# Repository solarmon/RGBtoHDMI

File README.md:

# RGBtoHDMI
RGBtoHDMI Projects

Various PCB projects based on c0pperdragon's Amiga adapter for hogetlet67's RGBtoHDMI solution to provide a HDMI output from the Denise chip digital signals on Amiga computers.

https://github.com/c0pperdragon/Amiga-Digital-Video

https://github.com/hoglet67/RGBtoHDMI

## Issues and Questions

Any issues or questions, please raise a ticket in the **Issues** section:

https://github.com/solarmon/RGBtoHDMI/issues

## Requirements

* Any Raspberry Pi Zero variant, but please note the following:
 - Raspberry Pi Zero 1.3 (original, no wireless, without a header, typically only one per purchase allowed)
 - Raspberry Pi Zero W (with **Wireless**, no header)
 - Raspberry Pi Zero WH (with **Wireless**, with **Header**)
* HDMI adapter/cable: 
 -The Raspberry Pi Zero comes with a **mini-HDMI** interface.
 - This needs needs to be mounted somewhere on, or passed through, the case.

## Audio not supported

The current RGBtoHDMI solutions do not support audio.

You will need to get audio to the HDMI display using some other method.

## OCS Display Modes Only

Only **OCS** display modes are supported, even when an ECS Denise is used.

**ECS** or **AGA** display modes are **not supported**.

## RGBtoHDMI Firmware for Raspberry Pi Zero

The official RGBtoHDMI firmware for the Raspberry Pi Zero can be downloaded from:

https://github.com/hoglet67/RGBtoHDMI/releases

Extract the zip file to the root of the micro-SD card.

Beta releases from IanSB can be downloaded from: 

https://github.com/IanSB/RGBtoHDMI/releases

These releases are sometimes required for certain features to work.

---
## CPLD Based Designs ##

These CPLD based boards are based on RGBtoHDMI CPLD design by LinuxJedi:

https://github.com/LinuxJedi/AmigaRGBtoHDMI

These don't require a Denise OCS/ECS jumper and have three menu button support.

I have added FF OSD integration support to the board.

A Quick Start Guide for these CPLD boards cane be found at:

https://github.com/solarmon/RGBtoHDMI/wiki/RGBtoHDMI-CPLD-Quick-Start-Guide

### RGBtoHDMI Amiga Denise DIP CPLD Rev 1.1 ###

More details and design files:

Rev 1.1: https://github.com/solarmon/RGBtoHDMI/tree/main/CPLD/RGBtoHDMI%20Amiga%20Denise%20DIP%20CPLD%20Rev%201.1

Rev 1.1 adds an optional additional right-angle push button for BT1.

Older revisions:

Rev 1.0: https://github.com/solarmon/RGBtoHDMI/tree/main/CPLD/RGBtoHDMI%20Amiga%20Denise%20DIP%20CPLD

## CPLD and FFC Based Designs ##

These CPLD based boards are based on the excellent RGBtoHDMI CPLD design by LinuxJedi:

https://github.com/LinuxJedi/AmigaRGBtoHDMI

These don't require a Denise OCS/ECS jumper and have three menu button support.

I have added FF OSD integration support to the board.

I have used an FFC connector design to allow for different breakout hats for different Denise packages (PLCC and DIP).

### RGBtoHDMI Amiga Denise CPLD FFC Rev 1.1 ###

More details and design files:

Rev 1.1: https://github.com/solarmon/RGBtoHDMI/tree/main/CPLD/RGBtoHDMI%20Amiga%20Denise%20CPLD%20FFC%20Rev%201.1

Rev 1.1 adds an optional additional right-angle push button for BT1.

Older revisions:

Rev 1.0: https://github.com/solarmon/RGBtoHDMI/tree/main/CPLD/RGBtoHDMI%20Amiga%20Denise%20CPLD%20FFC

### RGBtoHDMI Amiga Denise PLCC SMT Breakout FFC ###

More details and design files: https://github.com/solarmon/RGBtoHDMI/tree/main/CPLD/RGBtoHDMI%20Amiga%20Denise%20PLCC%20SMT%20Breakout%20FFC

### RGBtoHDMI Amiga Denise DIP Breakout FFC ###

More details and design files: https://github.com/solarmon/RGBtoHDMI/tree/main/CPLD/RGBtoHDMI%20Amiga%20Denise%20DIP%20Breakout%20FFC

### FF OSD Adapter - Rev 2 ##

More details and design files: https://github.com/solarmon/FlashFloppy/tree/main/FF%20OSD%20Adapter%20-%20Rev%202

The CPLD based RGBtoHDMI boards support FlashFloppy OSD integration and this is made easier with the FF OSD Adapter Rev 2 adapter.

---

## Amiga Denise DIP Adapter v2++

KiCAD design files:

https://github.com/solarmon/RGBtoHDMI/tree/main/RGBtoHDMI%20Amiga%20Denise%20-%20v2%2B%2B%20by%20solarmon

Based on on c0pperdragon's v2 adapter

https://github.com/c0pperdragon/Amiga-Digital-Video

https://github.com/hoglet67/RGBtoHDMI/tree/master/kicad_AmigaAdapter/V2

Tweaks and additions:

* Tweak to mask clearances
* Top and bottom ground plane
* Removes +3.3V regulator and uses the Raspberry Pi Zero +3.3V regulator
* Optional delay on PiCLK signal
* Support for FlashFloppy OSD

**Note**: The optional delay circuit (**U4**) for the **PiCLK** signal does not seem to do anything, so it is redundant and not required (but **JP2** still needs to be set to '**Normal PiCLK**'). It will be removed from future versions.

FlashFloppy OSD support is best used with the FlashFloppy OSD Blue Pill adapter at:

https://github.com/solarmon/FlashFloppy/tree/main/FF%20OSD%20Adapter

## Amiga Denise DIP Adapter v2++ Rev 2

KiCAD design files:

https://github.com/solarmon/RGBtoHDMI/tree/main/RGBtoHDMI%20Amiga%20Denise%20-%20v2%2B%2B%20by%20solarmon%20-%20Rev%202

This rev 2 design removes the redundant delay circuit using logic inverters, but adds the option to add a 47pF cap to the PiCLK line.

## Amiga Denise DIP Adapter - With Pi Relocation - Rev 1

**Note:** This is the **Rev 1** design - see further down for the **Rev 2** design.

**WARNING:** Uses an **SMT** socket header for the Raspberry Pi Zero

KiCAD design files:

https://github.com/solarmon/RGBtoHDMI/tree/main/RGBtoHDMI%20Amiga%20Denise%20-%20solarmon

A complete PCB redesign of the Amiga RGBtoHDMI v2 adapter by c0pperdragon.

Features:

* Raspberry Pi relocated to sit above the Odd CIA chip
* Use the Raspberry Pi Zero +3.3V regulator
* Optional delay on PiCLK signal
* Support for FlashFloppy OSD
* Uses an **SMT** socket header for the Raspberry Pi Zero

FlashFloppy OSD support is best used with the FlashFloppy OSD Blue Pill adapter at:

https://github.com/solarmon/FlashFloppy/tree/main/FF%20OSD%20Adapter

**Note**: The optional delay circuit (**U4**) for the **PiCLK** signal does not seem to do anything, so it is redundant and not required (but **JP2** still needs to be set to '**Normal PiCLK**'). It will be removed from future versions.

**Note**: **IMPORTANT** On this board design the Raspberry Pi Zero faces **up**. This is different from the original RGBtoHDMI v2 adapter where it faces **down**. This means the header is on the other side, so any existing Raspberry Pi Zero will need to be modified accordingly. **This will be changed in the next version to face down, so that existing Raspberry Pi Zeros can be used.**

**Note**: This board design still uses the smaller **TSSOP** package from the original RGBtoHDMI adapter. The next version will use the larger **SOIC** package.

## Amiga Denise DIP Adapter - With Pi Relocation - Rev 2 (TSSOP)

**WARNING:** Uses an **SMT** socket header for the Raspberry Pi Zero

KiCAD design files:

https://github.com/solarmon/RGBtoHDMI/tree/main/RGBtoHDMI%20Amiga%20Denise%20-%20solarmon%20-%20Rev%202%20-%20TSSOP

**Note:** This Rev 2 design has the Pi Zero facing **DOWN** (instead of facing **UP** in rev 1)

This rev 2 design removes the redundant delay circuit using logic inverters, but adds the option to add a 47pF cap to the PiCLK line.

This design still uses the smaller **TSSOP** chip package.

## Amiga Denise DIP Adapter - With Pi Relocation - Rev 2 (SOIC)

**WARNING:** Uses an **SMT** socket header for the Raspberry Pi Zero

KiCAD design files:

https://github.com/solarmon/RGBtoHDMI/tree/main/RGBtoHDMI%20Amiga%20Denise%20-%20solarmon%20-%20Rev%202%20-%20SOIC

**Note:** This Rev 2 design has the Pi Zero facing **DOWN** (instead of facing **UP** in rev 1)

**Note:** This version uses the larger SOIC chip package

This rev 2 design removes the redundant delay circuit using logic inverters, but adds the option to add a 47pF cap to the PiCLK line.

This design still uses the larger **SOIC** chip package, making it easier to hand solder.

## Amiga Denise PLCC Adapter

KiCAD design files:

https://github.com/solarmon/RGBtoHDMI/tree/main/RGBtoHDMI%20Amiga%20Denise%20ECS%20PLCC

Based on c0pperdragon's RGBtoHDMI Small adapter.

https://github.com/hoglet67/RGBtoHDMI/tree/master/kicad_AmigaAdapter/Small

This is a PLCC hat version of the RGBtoHDMI Small adapter that sits directly on top of the Denise PLCC chip.

This is for the Amiga A600 Denise ECS chip. However, the RGBtoHDMI solution only supports **OCS** modes, not **ECS** modes:

https://github.com/c0pperdragon/Amiga-Digital-Video#compatibility

**Note**: It uses the larger **SOIC** chip package, rather than the smaller **TSSOP** chip package.

Features:

* No soldering required - sits directly on top of the Denise PLCC chip
* Integrated RGBtoHDMI solution on same board.

**Note**: The +**5V** and **GND** traces going to the Denise PLCC chip is very thin. Header **JP1** is provided for +**5V** and **GND**. It is recommedned that power is provided to the board using this.

**Note**: The PLCC socket on this board needs some midifications to allow it to sit properly. See LemaruX's guide on the 68K PLCC socket rework that also applies to the Denise PLCC socket: 

https://github.com/LemaruX/Amiga-A600-68k-PLCC2DIP-v2/blob/main/PLCC-Rework.md

**Note**: This design will not work with most expansion boards in the A600 as it will spoil with it. Check compatibility before you commit to using/buying this board.

**Note**: On this board, the Raspberry Pi Zero faces **down**:

## RGBtoHDMI Pi Relocator Adapter  - Type A

KiCAD Design Files: https://github.com/solarmon/RGBtoHDMI/tree/main/RGBtoHDMI-Adapter%20Type%20A

This is a Pi relocator adapter that will flip it over to sit over RGBtoHDMI board.

**Note**: **IMPORTANT** The Raspberry Pi Zero is flipped over. To keep the profile low, you need to solder the Raspberry Pi Zero directly to the adapter.

## RGBtoHDMI Pi Relocator Adapter  - Type B Rev 2

KiCAD design Files: https://github.com/solarmon/RGBtoHDMI/tree/main/RGBtoHDMI-Adapter%20Type%20B%20Rev%202

This is a Pi relocator adapter and has an optional 47pF (or other value) location to reduce any sparkles.

## RGBtoHDMI Pi Relocator Adapter  - Type C Rev 2

KiCAD design Files: https://github.com/solarmon/RGBtoHDMI/tree/main/RGBtoHDMI-Adapter%20Type%20C%20Rev%202

This is a Pi relocator adapter and has an optional 47pF (or other value) location to reduce any sparkles.

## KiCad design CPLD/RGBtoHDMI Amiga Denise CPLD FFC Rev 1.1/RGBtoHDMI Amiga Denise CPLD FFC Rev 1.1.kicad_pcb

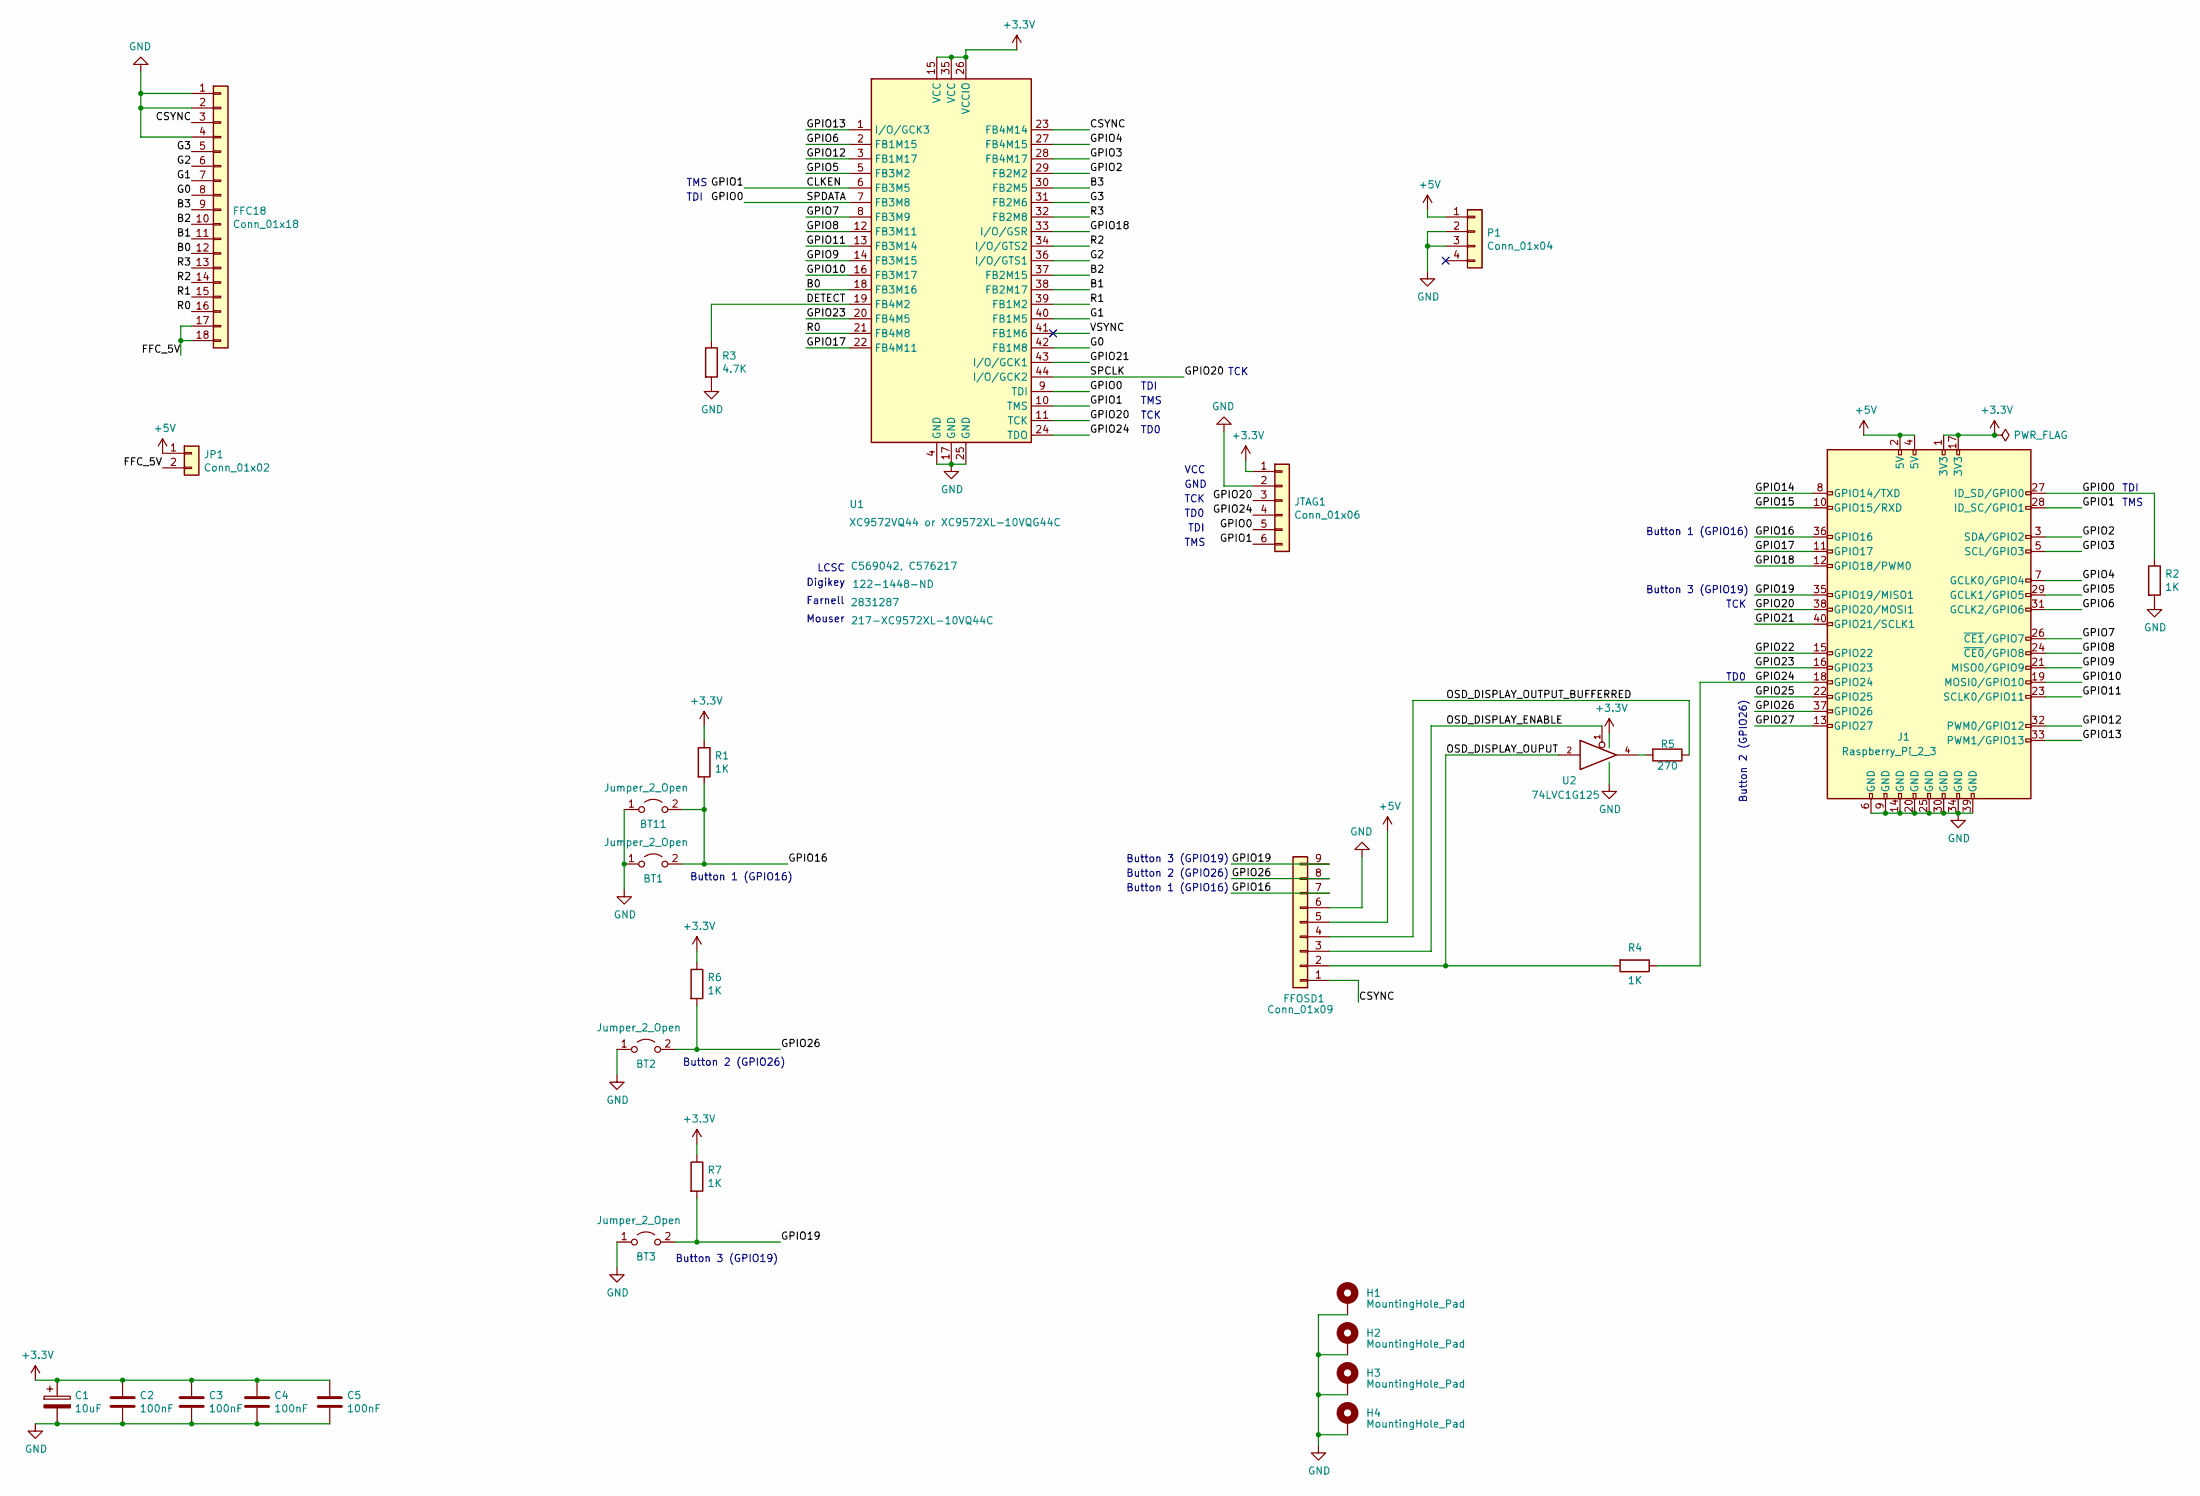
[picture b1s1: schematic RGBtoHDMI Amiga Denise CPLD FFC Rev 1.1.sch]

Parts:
BT1, BT2, BT3: Jumper_2_Open; PinHeader_1x02_P2.54mm_Horizontal
BT11: Jumper_2_Open; PUSH_BUTTON_RIGHT_ANGLE
C1: 10uF; C_0805_2012Metric_Pad1.18x1.45mm_HandSolder
C2, C3, C4, C5: 100nF; C_0805_2012Metric_Pad1.18x1.45mm_HandSolder
FFC18: Conn_01x18; FPC-SMD_X10B25U18T
FFOSD1: Conn_01x09; PinHeader_1x09_P2.54mm_Horizontal
H1, H2, H3, H4: MountingHole_Pad; MountingHole_3.2mm_M3_Pad_Via
J1: Raspberry_Pi_2_3; PinSocket_2x20_P2.54mm_Vertical
JP1: Conn_01x02; PinHeader_1x02_P2.54mm_Horizontal
JTAG1: Conn_01x06; PinHeader_1x06_P2.54mm_Vertical
P1: Conn_01x04; PinHeader_1x04_P2.54mm_Horizontal
R1, R2, R4, R6, R7: 1K; R_0805_2012Metric_Pad1.20x1.40mm_HandSolder
R3: 4.7K; R_0805_2012Metric_Pad1.20x1.40mm_HandSolder
R5: 270; R_0805_2012Metric_Pad1.20x1.40mm_HandSolder
U1: XC9572VQ44 or XC9572XL-10VQG44C; TQFP-44_10x10mm_P0.8mm; LCSC C569042, C576217
U2: 74LVC1G125; SOT-753

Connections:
+3V3: C1.1, C2.1, C3.1, C4.1, C5.1, J1.1 (3V3), J1.17 (3V3), JTAG1.1, R1.1, R6.1, R7.1, U1.15 (VCC), U1.26 (VCCIO), U1.35 (VCC), U2.5 (VCC)
+5V: FFOSD1.5, J1.2 (5V), J1.4 (5V), JP1.1, P1.1
/B0: FFC18.12, U1.18 (FB3M16)
/B1: FFC18.11, U1.38 (FB2M17)
/B2: FFC18.10, U1.37 (FB2M15)
/B3: FFC18.9, U1.30 (FB2M5)
/CLKEN: J1.28 (ID_SC/GPIO1), JTAG1.6, U1.6 (FB3M5), U1.10 (TMS)
/CSYNC: FFC18.3, FFOSD1.1, U1.23 (FB4M14)
/DETECT: R3.1, U1.19 (FB4M2)
/FFC_5V: FFC18.17, FFC18.18, JP1.2
/G0: FFC18.8, U1.42 (FB1M8)
/G1: FFC18.7, U1.40 (FB1M5)
/G2: FFC18.6, U1.36 (I/O/GTS1)
/G3: FFC18.5, U1.31 (FB2M6)
/GPIO0: J1.27 (ID_SD/GPIO0), JTAG1.5, R2.1, U1.7 (FB3M8), U1.9 (TDI)
/GPIO2: J1.3 (SDA/GPIO2), U1.29 (FB2M2)
/GPIO3: J1.5 (SCL/GPIO3), U1.28 (FB4M17)
/GPIO4: J1.7 (GCLK0/GPIO4), U1.27 (FB4M15)
/GPIO5: J1.29 (GCLK1/GPIO5), U1.5 (FB3M2)
/GPIO6: J1.31 (GCLK2/GPIO6), U1.2 (FB1M15)
/GPIO7: J1.26 (~CE1~/GPIO7), U1.8 (FB3M9)
/GPIO8: J1.24 (~CE0~/GPIO8), U1.12 (FB3M11)
/GPIO9: J1.21 (MISO0/GPIO9), U1.14 (FB3M15)
/GPIO10: J1.19 (MOSI0/GPIO10), U1.16 (FB3M17)
/GPIO11: J1.23 (SCLK0/GPIO11), U1.13 (FB3M14)
/GPIO12: J1.32 (PWM0/GPIO12), U1.3 (FB1M17)
/GPIO13: J1.33 (PWM1/GPIO13), U1.1 (I/O/GCK3)
/GPIO14: J1.8 (GPIO14/TXD)
/GPIO15: J1.10 (GPIO15/RXD)
/GPIO16: BT1.2 (B), BT11.2 (B), FFOSD1.7, J1.36 (GPIO16), R1.2
/GPIO17: J1.11 (GPIO17), U1.22 (FB4M11)
/GPIO18: J1.12 (GPIO18/PWM0), U1.33 (I/O/GSR)
/GPIO19: BT3.2 (B), FFOSD1.9, J1.35 (GPIO19/MISO1), R7.2
/GPIO20: J1.38 (GPIO20/MOSI1), JTAG1.3, U1.11 (TCK), U1.44 (I/O/GCK2)
/GPIO21: J1.40 (GPIO21/SCLK1), U1.43 (I/O/GCK1)
/GPIO22: J1.15 (GPIO22)
/GPIO23: J1.16 (GPIO23), U1.20 (FB4M5)
/GPIO24: J1.18 (GPIO24), JTAG1.4, R4.1, U1.24 (TDO)
/GPIO25: J1.22 (GPIO25)
/GPIO26: BT2.2 (B), FFOSD1.8, J1.37 (GPIO26), R6.2
/GPIO27: J1.13 (GPIO27)
/OSD_DISPLAY_ENABLE: FFOSD1.3, U2.1
/OSD_DISPLAY_OUPUT: FFOSD1.2, R4.2, U2.2
/OSD_DISPLAY_OUTPUT_BUFFERRED: FFOSD1.4, R5.1
/R0: FFC18.16, U1.21 (FB4M8)
/R1: FFC18.15, U1.39 (FB1M2)
/R2: FFC18.14, U1.34 (I/O/GTS2)
/R3: FFC18.13, U1.32 (FB2M8)
/VSYNC: U1.41 (FB1M6)
GND: BT1.1 (A), BT2.1 (A), BT3.1 (A), BT11.1 (A), C1.2, C2.2, C3.2, C4.2, C5.2, FFC18.1, FFC18.2, FFC18.4, FFOSD1.6, H1.1, H2.1, H3.1, H4.1, J1.6 (GND), J1.9 (GND), J1.14 (GND), J1.20 (GND), J1.25 (GND), J1.30 (GND), J1.34 (GND), J1.39 (GND), JTAG1.2, P1.2, P1.3, R2.2, R3.2, U1.4 (GND), U1.17 (GND), U1.25 (GND), U2.3 (GND)
unnamed: R5.2, U2.4

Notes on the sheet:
TD0
TCK
TMS
TDI
GND
VCC
Button 1 (GPIO16)
Button 2 (GPIO26)
Button 3 (GPIO19)
Farnell
Digikey
LCSC
Mouser

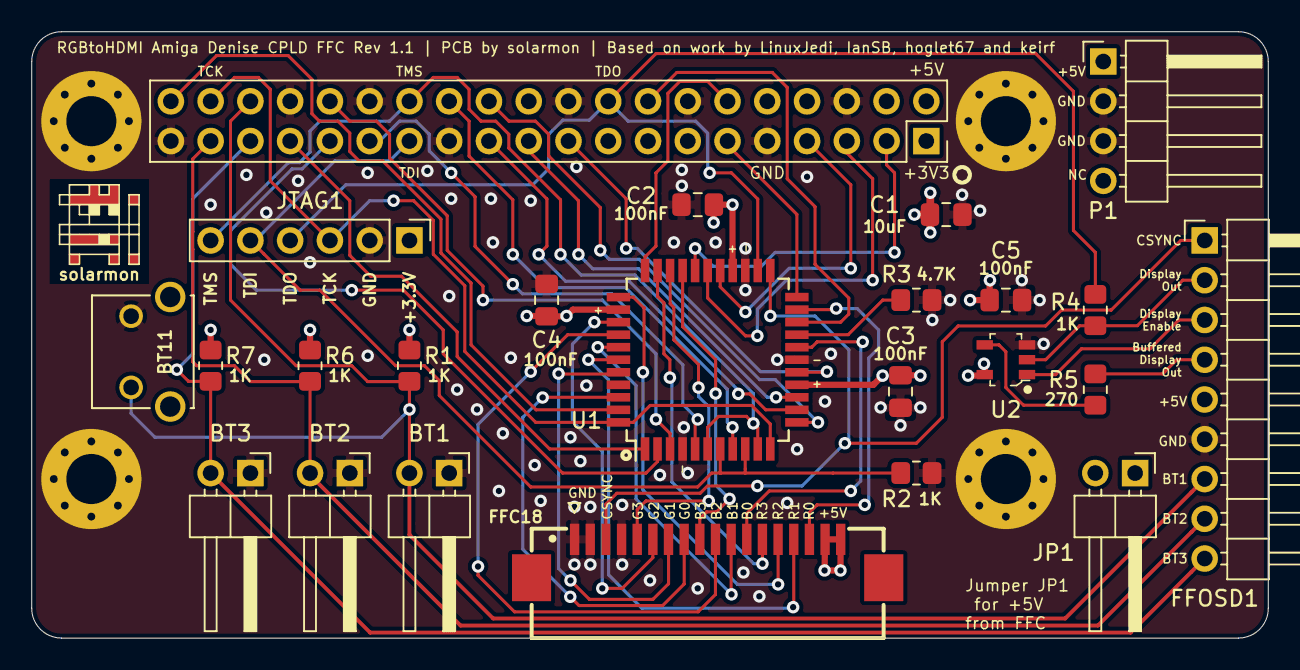
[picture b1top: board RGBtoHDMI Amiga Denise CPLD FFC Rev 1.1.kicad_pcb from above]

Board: 2 copper layers, 79.0 x 38.7 mm, 29 parts (0 on the bottom side), 45 nets.

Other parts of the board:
solarmon: solarmon-logo-25mils

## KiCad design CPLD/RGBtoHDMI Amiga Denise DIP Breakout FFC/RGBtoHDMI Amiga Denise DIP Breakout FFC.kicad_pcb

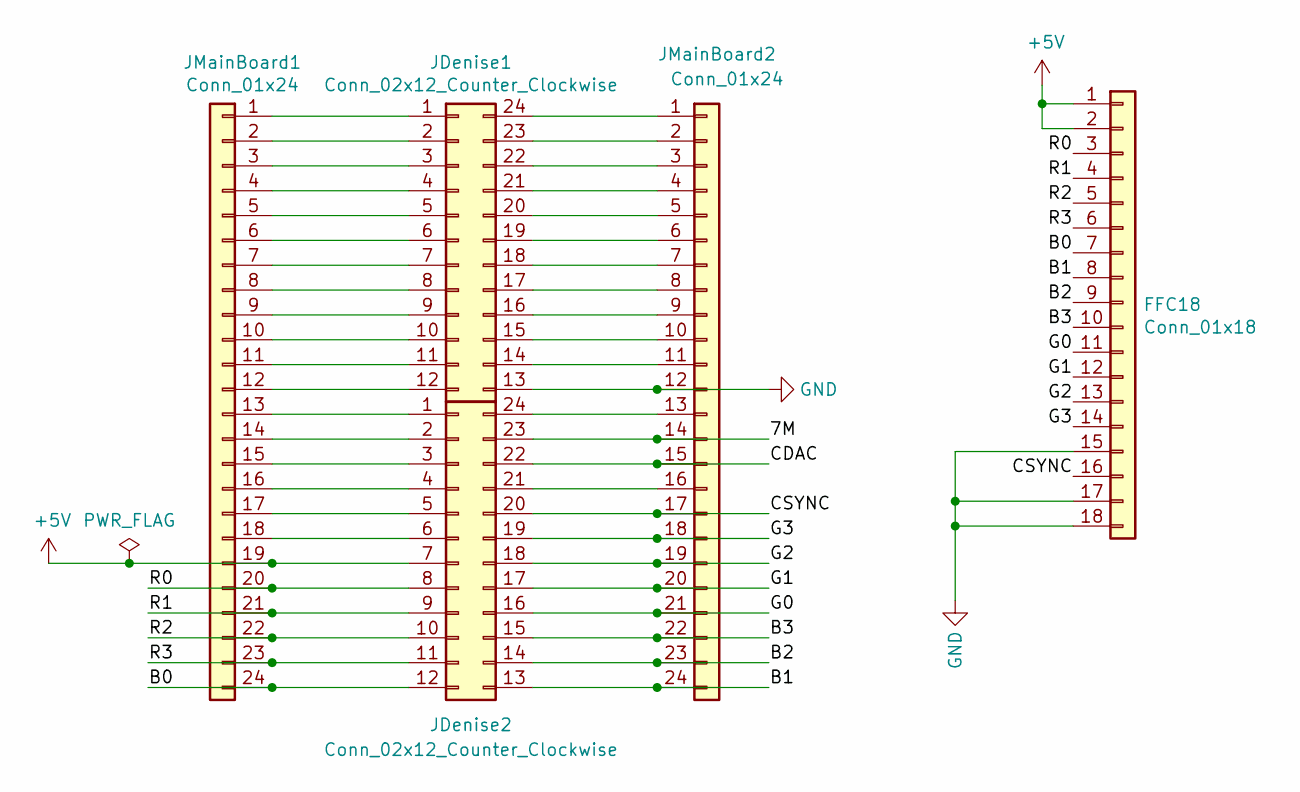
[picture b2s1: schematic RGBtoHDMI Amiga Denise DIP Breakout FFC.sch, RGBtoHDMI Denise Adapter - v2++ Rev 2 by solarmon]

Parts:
FFC18: Conn_01x18; FPC-SMD_X10B25U18T
JDenise1, JDenise2: Conn_02x12_Counter_Clockwise; DIP-24_W15.24mm_Socket
JMainBoard1, JMainBoard2: Conn_01x24; PinHeader_1x24_P2.54mm_Vertical_smaller

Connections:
+5V: FFC18.1, FFC18.2, JDenise2.7, JMainBoard1.19
/7M: JDenise2.23, JMainBoard2.14
/B0: FFC18.7, JDenise2.12, JMainBoard1.24
/B1: FFC18.8, JDenise2.13, JMainBoard2.24
/B2: FFC18.9, JDenise2.14, JMainBoard2.23
/B3: FFC18.10, JDenise2.15, JMainBoard2.22
/CDAC: JDenise2.22, JMainBoard2.15
/CSYNC: FFC18.16, JDenise2.20, JMainBoard2.17
/G0: FFC18.11, JDenise2.16, JMainBoard2.21
/G1: FFC18.12, JDenise2.17, JMainBoard2.20
/G2: FFC18.13, JDenise2.18, JMainBoard2.19
/G3: FFC18.14, JDenise2.19, JMainBoard2.18
/R0: FFC18.3, JDenise2.8, JMainBoard1.20
/R1: FFC18.4, JDenise2.9, JMainBoard1.21
/R2: FFC18.5, JDenise2.10, JMainBoard1.22
/R3: FFC18.6, JDenise2.11, JMainBoard1.23
GND: FFC18.15, FFC18.17, FFC18.18, FFC18.MP, JDenise1.13, JMainBoard2.12
unnamed: JDenise1.1, JMainBoard1.1
unnamed: JDenise1.2, JMainBoard1.2
unnamed: JDenise1.3, JMainBoard1.3
unnamed: JDenise1.4, JMainBoard1.4
unnamed: JDenise1.5, JMainBoard1.5
unnamed: JDenise1.6, JMainBoard1.6
unnamed: JDenise1.7, JMainBoard1.7
unnamed: JDenise1.8, JMainBoard1.8
unnamed: JDenise1.9, JMainBoard1.9
unnamed: JDenise1.10, JMainBoard1.10
unnamed: JDenise1.11, JMainBoard1.11
unnamed: JDenise1.12, JMainBoard1.12
unnamed: JDenise1.14, JMainBoard2.11
unnamed: JDenise1.15, JMainBoard2.10
unnamed: JDenise1.16, JMainBoard2.9
unnamed: JDenise1.17, JMainBoard2.8
unnamed: JDenise1.18, JMainBoard2.7
unnamed: JDenise1.19, JMainBoard2.6
unnamed: JDenise1.20, JMainBoard2.5
unnamed: JDenise1.21, JMainBoard2.4
unnamed: JDenise1.22, JMainBoard2.3
unnamed: JDenise1.23, JMainBoard2.2
unnamed: JDenise1.24, JMainBoard2.1
unnamed: JDenise2.1, JMainBoard1.13
unnamed: JDenise2.2, JMainBoard1.14
unnamed: JDenise2.3, JMainBoard1.15
unnamed: JDenise2.4, JMainBoard1.16
unnamed: JDenise2.5, JMainBoard1.17
unnamed: JDenise2.6, JMainBoard1.18
unnamed: JDenise2.21, JMainBoard2.16
unnamed: JDenise2.24, JMainBoard2.13

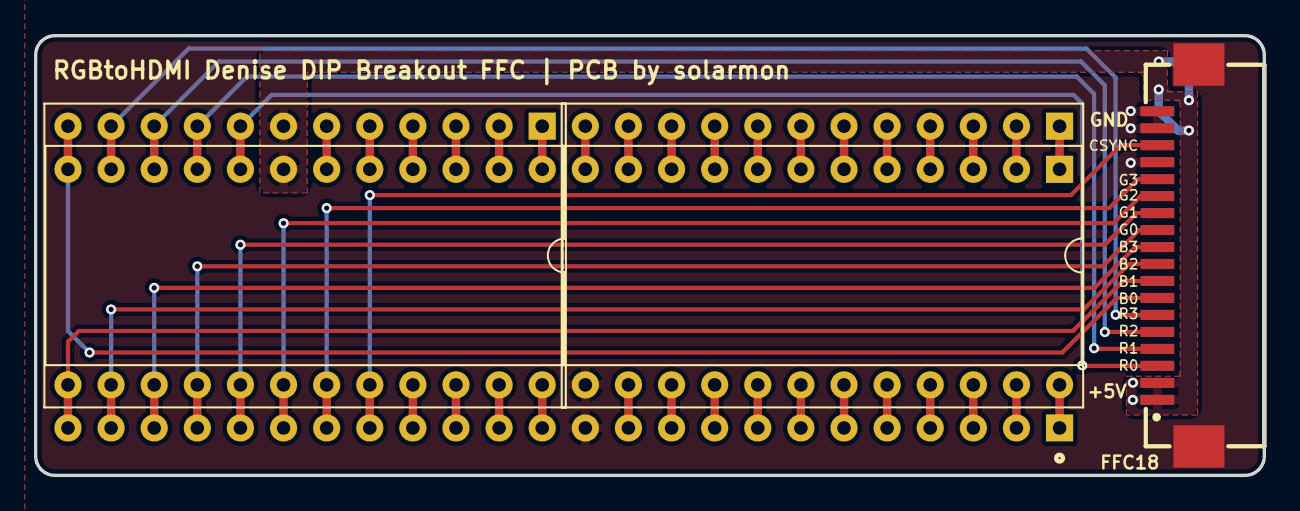
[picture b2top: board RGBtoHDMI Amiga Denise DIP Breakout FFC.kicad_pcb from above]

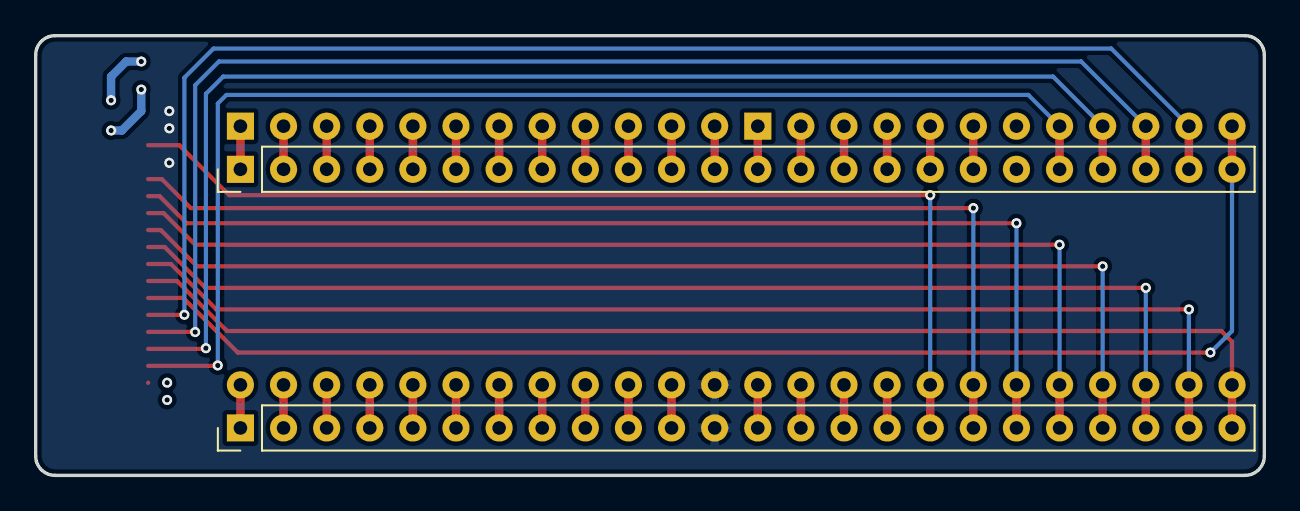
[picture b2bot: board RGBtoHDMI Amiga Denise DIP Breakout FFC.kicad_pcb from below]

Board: 2 copper layers, 72.4 x 25.9 mm, 5 parts (2 on the bottom side), 48 nets.

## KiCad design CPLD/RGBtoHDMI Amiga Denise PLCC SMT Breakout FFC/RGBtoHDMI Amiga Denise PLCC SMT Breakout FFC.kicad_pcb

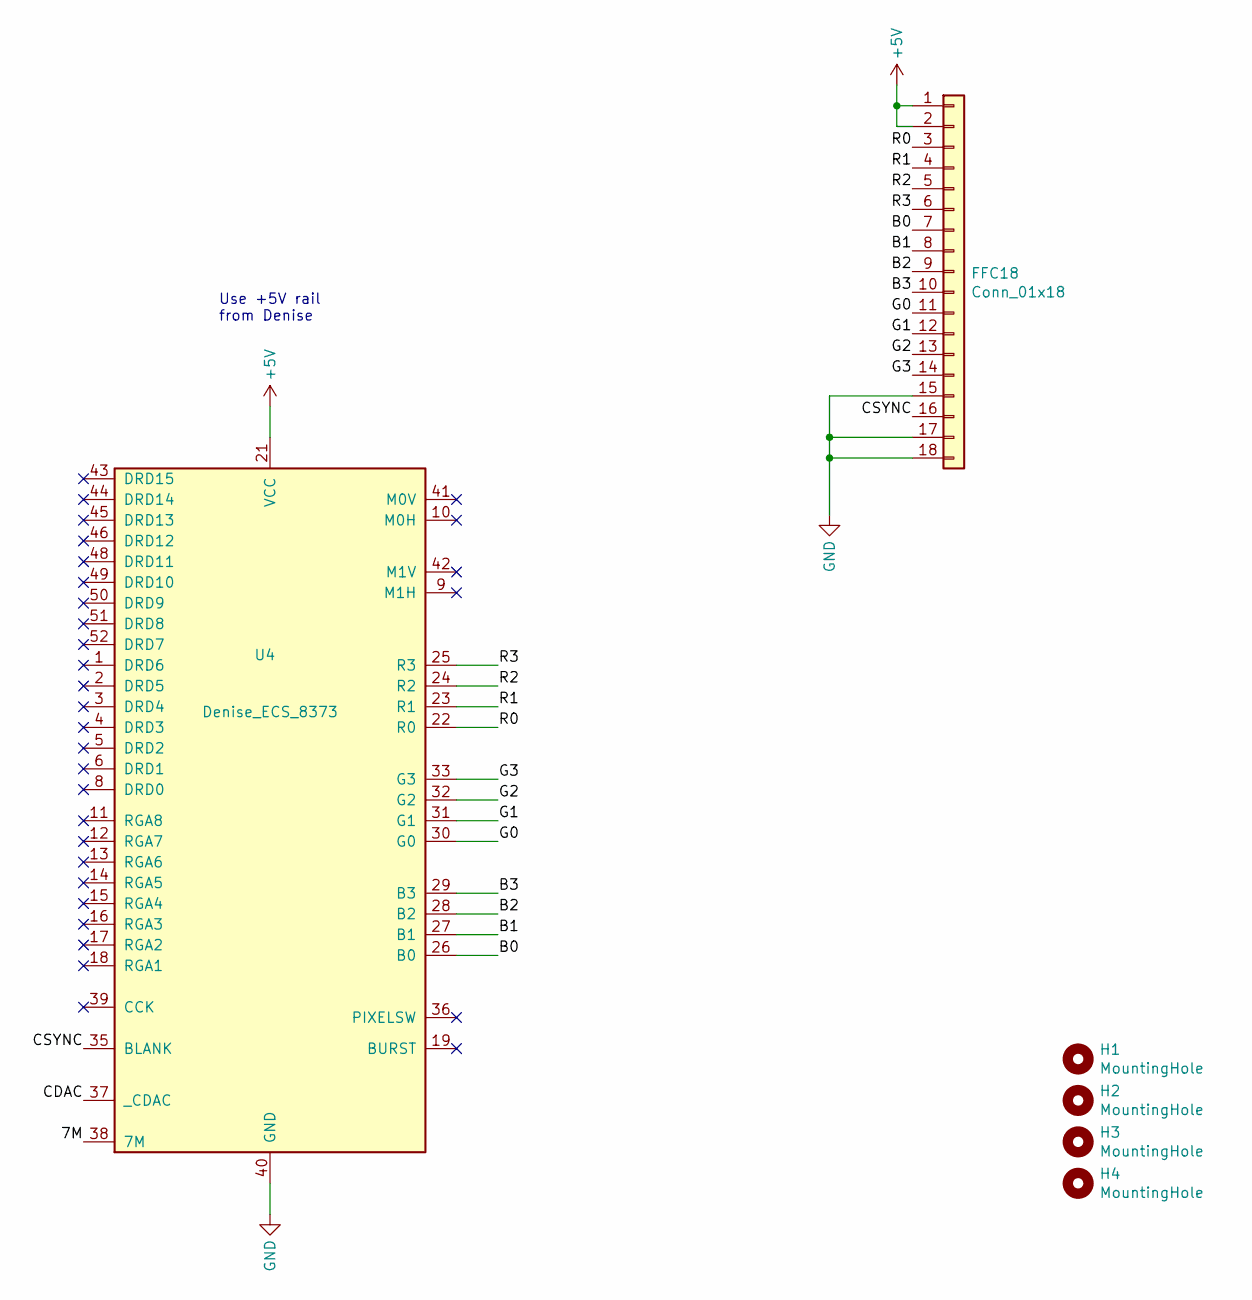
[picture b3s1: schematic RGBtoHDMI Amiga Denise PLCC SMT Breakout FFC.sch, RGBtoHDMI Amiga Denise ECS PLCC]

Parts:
FFC18: Conn_01x18; FPC-SMD_X10B25U18T
H1, H2, H3, H4: MountingHole; MountingHole_4.3mm_M4
U4: Denise_ECS_8373; PLCC-52_SMD-Socket_Reversed_Hat

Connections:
+5V: FFC18.1, FFC18.2, U4.21 (VCC)
/7M: U4.38 (7M)
/B0: FFC18.7, U4.26 (B0)
/B1: FFC18.8, U4.27 (B1)
/B2: FFC18.9, U4.28 (B2)
/B3: FFC18.10, U4.29 (B3)
/CDAC: U4.37 (_CDAC)
/CSYNC: FFC18.16, U4.35 (BLANK)
/G0: FFC18.11, U4.30 (G0)
/G1: FFC18.12, U4.31 (G1)
/G2: FFC18.13, U4.32 (G2)
/G3: FFC18.14, U4.33 (G3)
/R0: FFC18.3, U4.22 (R0)
/R1: FFC18.4, U4.23 (R1)
/R2: FFC18.5, U4.24 (R2)
/R3: FFC18.6, U4.25 (R3)
GND: FFC18.15, FFC18.17, FFC18.18, FFC18.MP, U4.40 (GND)

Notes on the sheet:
Use +5V rail from Denise

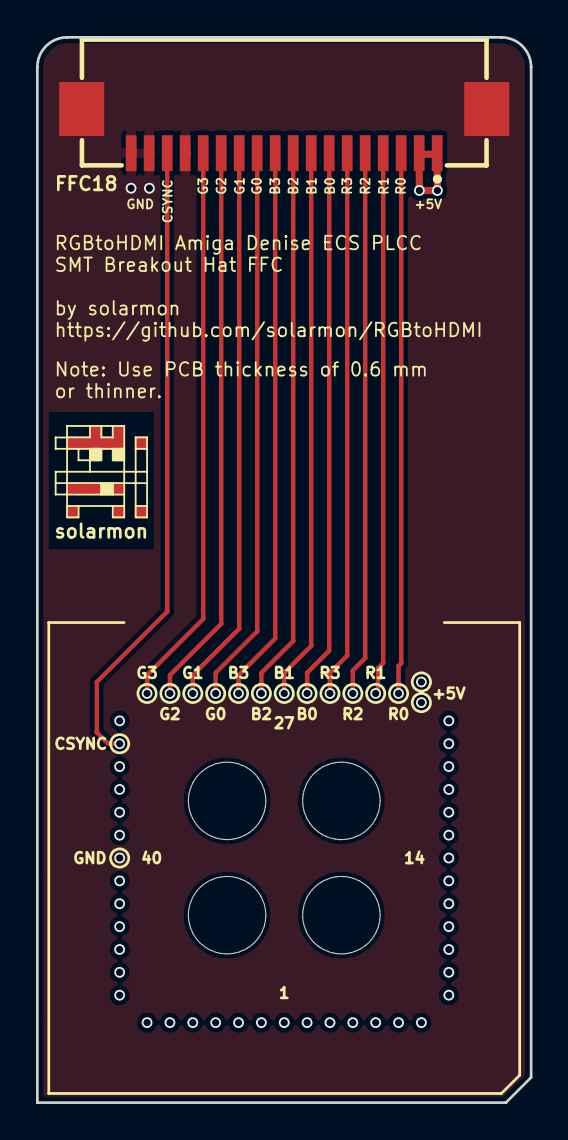
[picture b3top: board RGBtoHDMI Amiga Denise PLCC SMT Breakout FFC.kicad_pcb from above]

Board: 2 copper layers, 27.4 x 59.2 mm, 7 parts (1 on the bottom side), 15 nets.

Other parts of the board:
solarmon: solarmon-logo-25mils

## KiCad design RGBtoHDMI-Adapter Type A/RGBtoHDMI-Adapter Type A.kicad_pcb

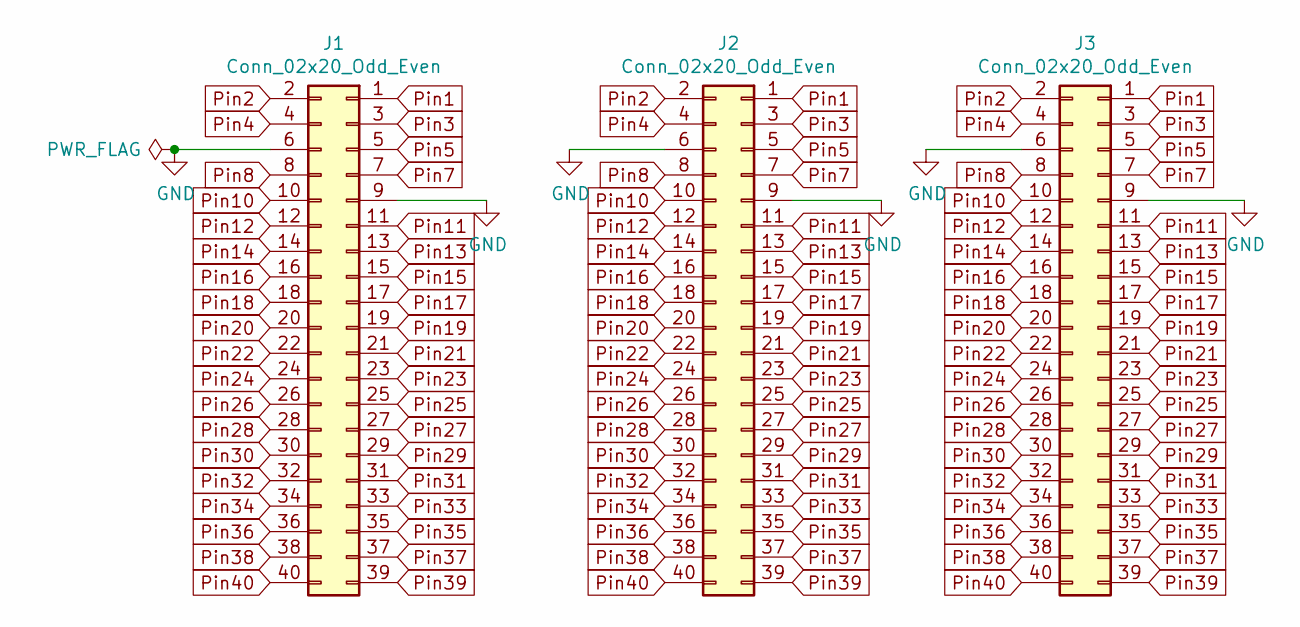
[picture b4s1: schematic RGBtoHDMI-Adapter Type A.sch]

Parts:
J1: Conn_02x20_Odd_Even; PinHeader_2x20_P2.54mm_Vertical
J2, J3: Conn_02x20_Odd_Even; PinSocket_2x20_P2.54mm_Vertical

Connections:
GND: J1.6, J1.9, J2.6, J2.9, J3.6, J3.9
Pin1: J1.1, J2.1, J3.1
Pin2: J1.2, J2.2, J3.2
Pin3: J1.3, J2.3, J3.3
Pin4: J1.4, J2.4, J3.4
Pin5: J1.5, J2.5, J3.5
Pin7: J1.7, J2.7, J3.7
Pin8: J1.8, J2.8, J3.8
Pin10: J1.10, J2.10, J3.10
Pin11: J1.11, J2.11, J3.11
Pin12: J1.12, J2.12, J3.12
Pin13: J1.13, J2.13, J3.13
Pin14: J1.14, J2.14, J3.14
Pin15: J1.15, J2.15, J3.15
Pin16: J1.16, J2.16, J3.16
Pin17: J1.17, J2.17, J3.17
Pin18: J1.18, J2.18, J3.18
Pin19: J1.19, J2.19, J3.19
Pin20: J1.20, J2.20, J3.20
Pin21: J1.21, J2.21, J3.21
Pin22: J1.22, J2.22, J3.22
Pin23: J1.23, J2.23, J3.23
Pin24: J1.24, J2.24, J3.24
Pin25: J1.25, J2.25, J3.25
Pin26: J1.26, J2.26, J3.26
Pin27: J1.27, J2.27, J3.27
Pin28: J1.28, J2.28, J3.28
Pin29: J1.29, J2.29, J3.29
Pin30: J1.30, J2.30, J3.30
Pin31: J1.31, J2.31, J3.31
Pin32: J1.32, J2.32, J3.32
Pin33: J1.33, J2.33, J3.33
Pin34: J1.34, J2.34, J3.34
Pin35: J1.35, J2.35, J3.35
Pin36: J1.36, J2.36, J3.36
Pin37: J1.37, J2.37, J3.37
Pin38: J1.38, J2.38, J3.38
Pin39: J1.39, J2.39, J3.39
Pin40: J1.40, J2.40, J3.40

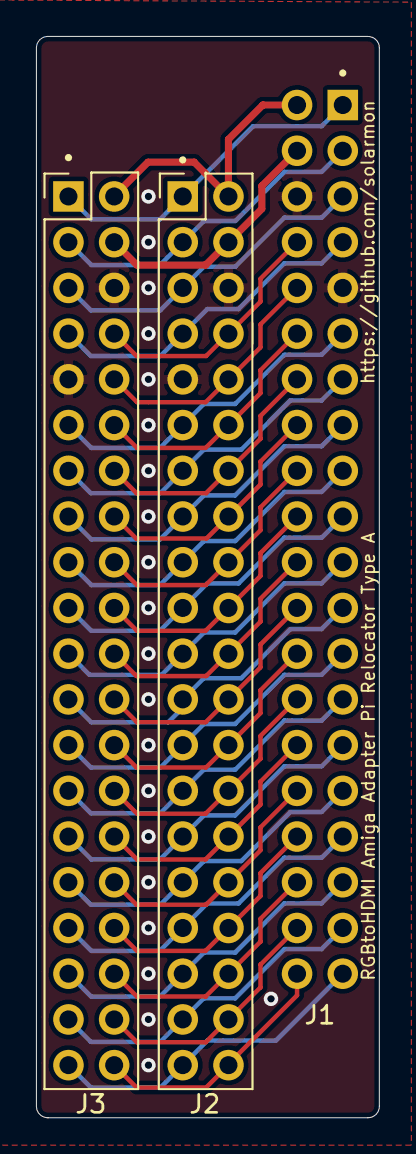
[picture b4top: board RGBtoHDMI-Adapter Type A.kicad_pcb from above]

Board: 2 copper layers, 19.0 x 60.1 mm, 3 parts (1 on the bottom side), 39 nets.

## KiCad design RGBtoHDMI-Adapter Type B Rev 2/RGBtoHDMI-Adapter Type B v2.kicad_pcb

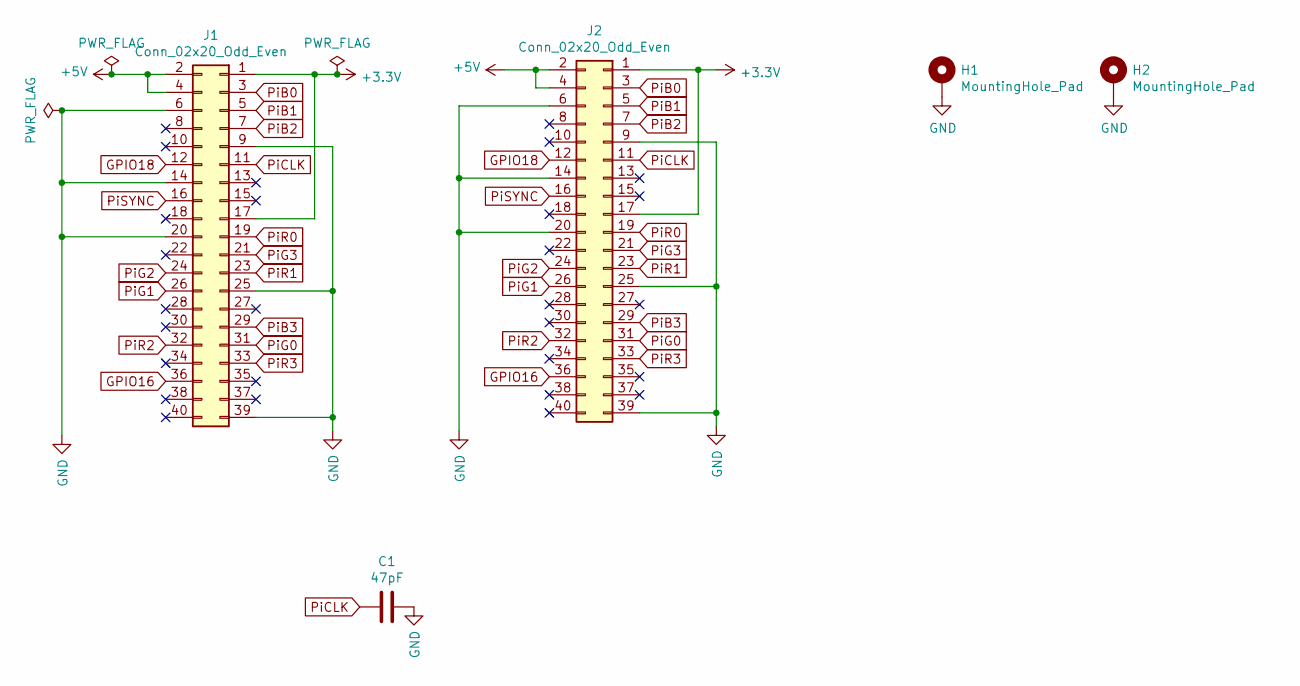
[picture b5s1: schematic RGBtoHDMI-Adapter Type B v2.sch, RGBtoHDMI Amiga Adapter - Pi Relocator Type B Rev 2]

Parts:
C1: 47pF; C_0805_2012Metric_Pad1.18x1.45mm_HandSolder
H1, H2: MountingHole_Pad; MountingHole_3.2mm_M3_ISO7380_Pad
J1: Conn_02x20_Odd_Even; PinHeader_2x20_P2.54mm_Vertical
J2: Conn_02x20_Odd_Even; PinSocket_2x20_P2.54mm_Vertical

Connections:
+3V3: J1.1, J1.17, J2.1, J2.17
+5V: J1.2, J1.4, J2.2, J2.4
GND: C1.1, H1.1, H2.1, J1.6, J1.9, J1.14, J1.20, J1.25, J1.39, J2.6, J2.9, J2.14, J2.20, J2.25, J2.39
GPIO16: J1.36, J2.36
GPIO18: J1.12, J2.12
PiB0: J1.3, J2.3
PiB1: J1.5, J2.5
PiB2: J1.7, J2.7
PiB3: J1.29, J2.29
PiCLK: C1.2, J1.11, J2.11
PiG0: J1.31, J2.31
PiG1: J1.26, J2.26
PiG2: J1.24, J2.24
PiG3: J1.21, J2.21
PiR0: J1.19, J2.19
PiR1: J1.23, J2.23
PiR2: J1.32, J2.32
PiR3: J1.33, J2.33
PiSYNC: J1.16, J2.16

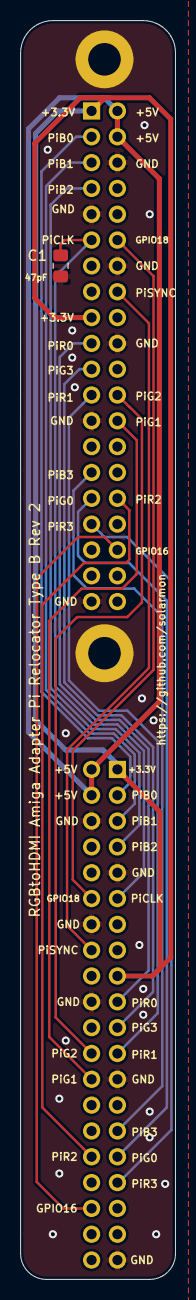
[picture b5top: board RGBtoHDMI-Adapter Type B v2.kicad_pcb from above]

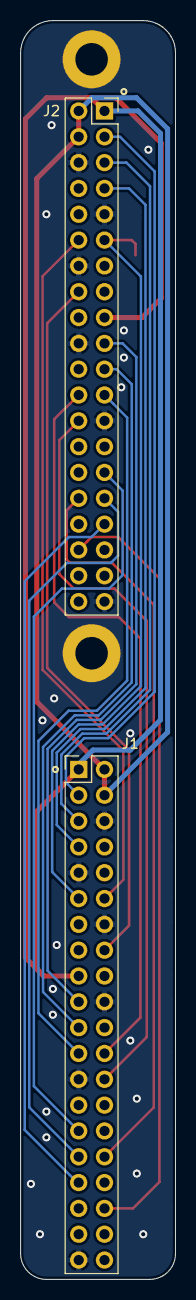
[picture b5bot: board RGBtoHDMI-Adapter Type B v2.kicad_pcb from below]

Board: 2 copper layers, 15.2 x 123.8 mm, 5 parts (2 on the bottom side), 19 nets.

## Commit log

2021-04-10 Added KiCAD project files
2021-04-10 Enabled Pi 3D model
2021-04-10 Added picture of Pi facing UP
2021-04-10 Added Pi facing down picture, for PLCC version.
2021-04-10 Added FF OSD Blue Pill adapter photo and link
2021-04-11 Added some more info about redundant U4
2021-04-11 Added "RGBtoHDMI-Adapter Type C Rev 2"
2021-04-11 Added Pi relocator adapter - Type C Rev 2
2021-04-11 Updated cap value to 47pF
2021-04-11 Uploaded screenshot of relocator board
2021-04-11 Added "RGBtoHDMI-Adapter Type B Rev 2"
2021-04-11 Added RGBtoHDMI Pi Relocator Adapter - Type B Rev 2
2021-04-11 Added RGBtoHDMI-Adapter Type A
2021-04-11 RGBtoHDMI Pi Relocator Adapter - Type A
2021-04-27 Added rev 2 TSSOP and SOIC boards
2021-04-27 Added rev 2 TSSOP and SOIC designs
2021-04-27 Added note about Rev 1 and Rev 2
2021-04-27 Added RGBtoHDMI Amiga Denise - v2++ by solarmon - Rev 2
2021-04-27 Added text for RGBtoHDMI Amiga Denise - v2++ by solarmon - Rev 2
2021-04-27 Corrected U1 label orientation
2021-04-28 Added warning about SMD socket header for Pi Zero
2021-04-28 Changed SMD to SMT
2021-06-05 Added CPLD based designs
    Added CPLD based designs:
    * RGBtoHDMI Amiga Denise CPLD FFC
    * RGBtoHDMI Amiga Denise DIP Breakout FFC
    * RGBtoHDMI Amiga Denise DIP CPLD
    * RGBtoHDMI Amiga Denise PLCC SMT Breakout FFC
2021-06-05 Added CPLD/FFC based designs
2021-06-05 Added link to LinuxJedi
2021-06-17 Added QR code
2021-06-23 Added CPLD-Recovery-Menu.jpg
2021-07-24 Linked to FF OSD Adapter - Rev 2
2021-07-27 Added top image with Pi
2021-07-27 Added top images with Pi
2021-08-15 Added Rev 1.1 versions
2021-08-15 Updated for CPLD Rev 1.1 boards
2022-01-18 Updated Denise PLCC adapter image
